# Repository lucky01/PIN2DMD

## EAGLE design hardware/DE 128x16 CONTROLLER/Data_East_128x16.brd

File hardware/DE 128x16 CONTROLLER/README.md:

# PIN2DMD - 128x16 DOT MATRIX CONTROLLER BOARD

This are the PCB files for the Dot Matrix Contoller Board like used in early Data East machines 
e.g Batman, Checkpoint, Hook, Star Trek 25th anniversary and Teenage Mutant Ninja Turtles. It is needed to connect these
machines to the PIN2DMD Nucleo shield. PCB design by Rappelbox, UncleSash and Lucky1

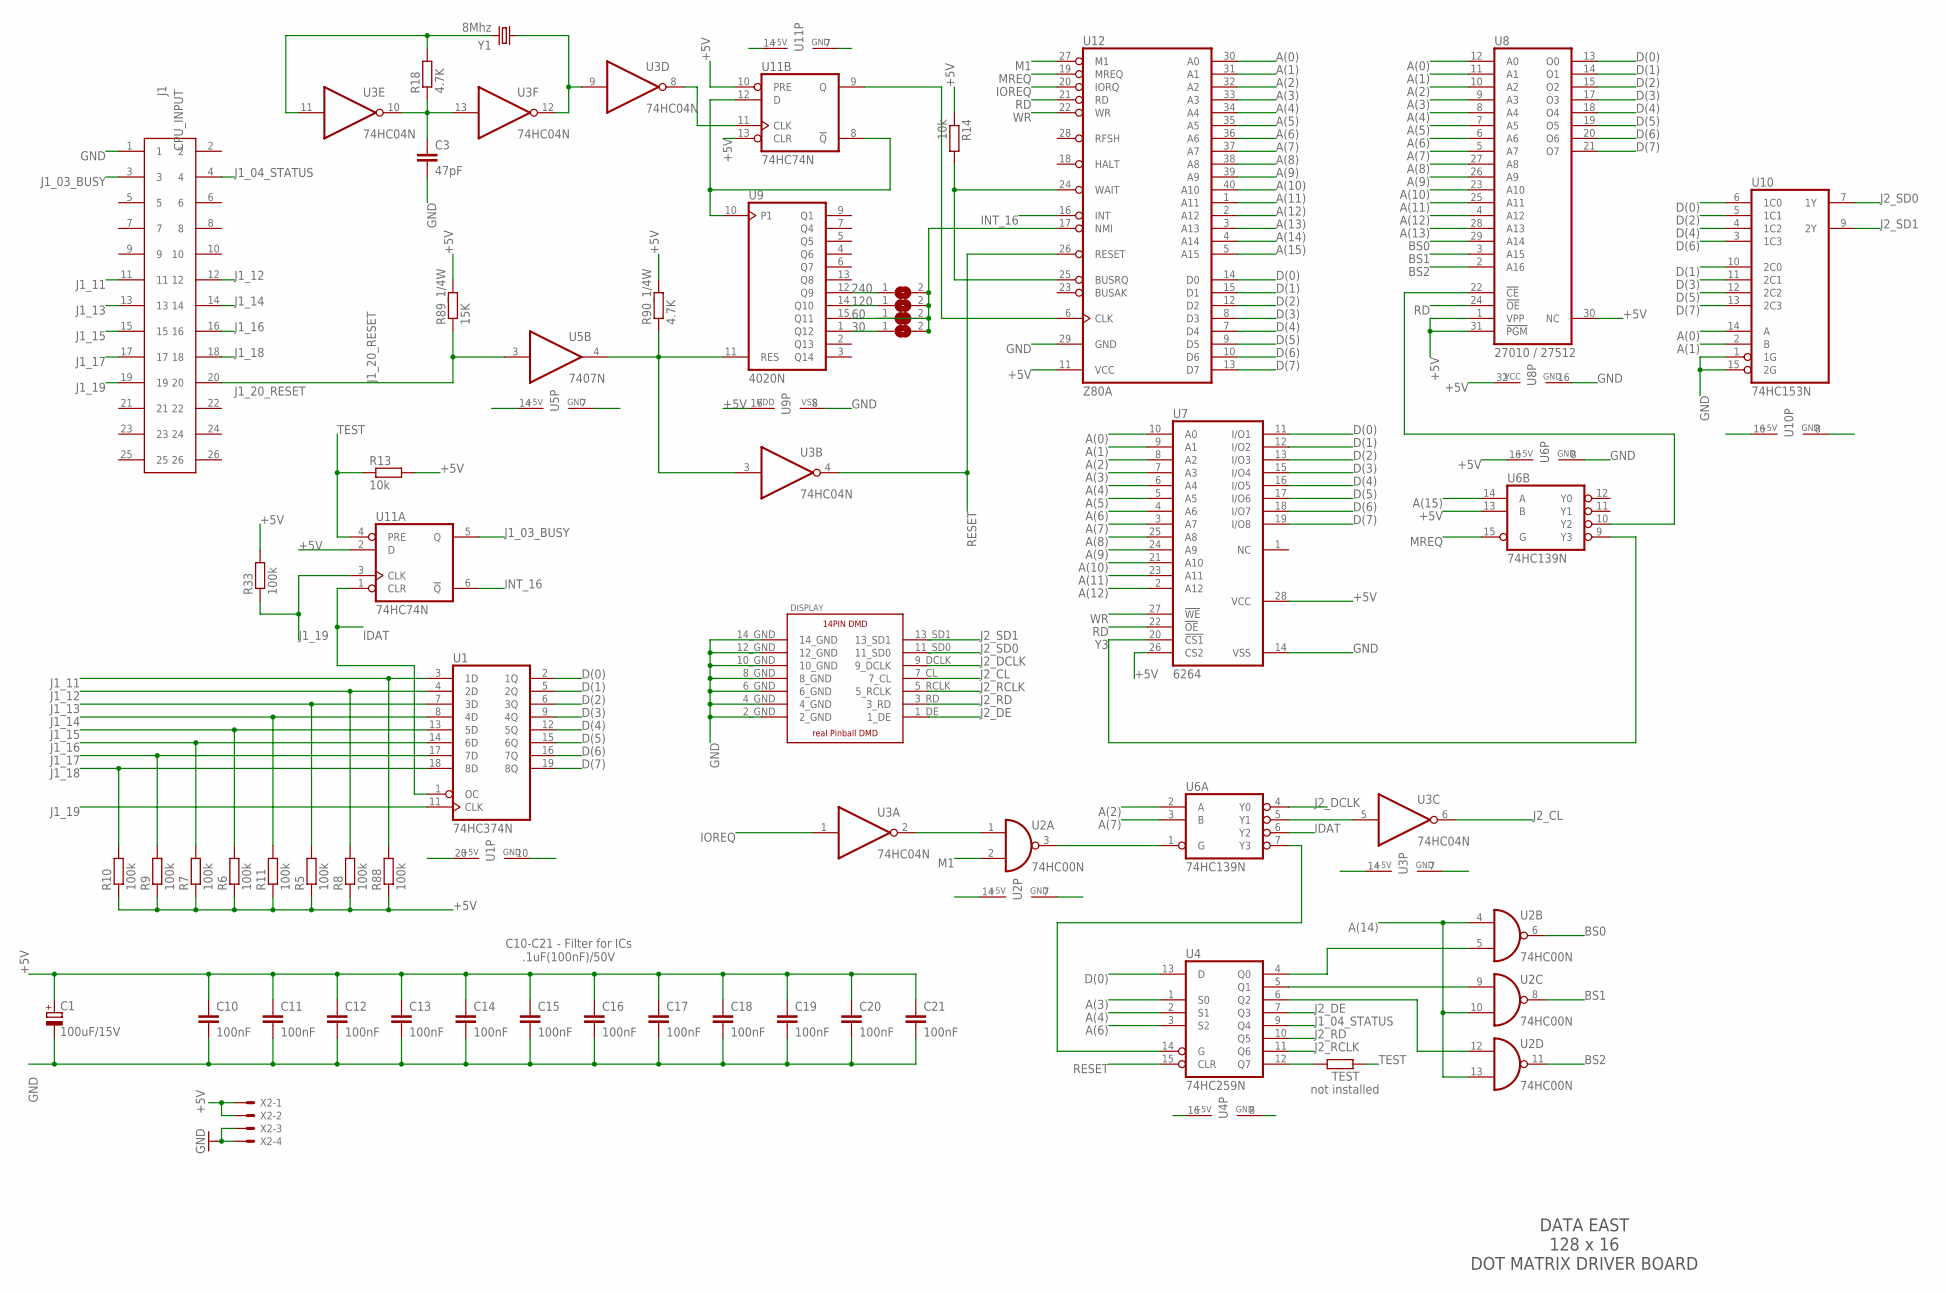
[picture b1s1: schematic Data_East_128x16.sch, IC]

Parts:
C1: 100uF/15V; E2,5-7
C3: 47pF; C050-025X075
C10, C11, C12, C13, C14, C15, C16, C17, C18, C19, C20, C21: 100nF; C050-025X075
CPU_INPUT: J1; 61202622323
DISPLAY: PINBALL_DMD_HEADER_MALE; 14_PIN_DMD_MALE
R5, R6, R7, R8, R9, R10, R11, R33, R88: 100k; 0207/7
R13, R14: 10k; 0207/7
R18, R90_1/4W: 4.7K; 0207/7
R89_1/4W: 15K; 0207/7
SJ2, SJ4, SJ5, SJ6: SJ
TEST: R-EU_0207/7; 0207/7
U1: 74HC374N; DIL20
U2: 74HC00N; DIL14
U3: 74HC04N; DIL14
U4: 74HC259N; DIL16
U5: 7407N; DIL14
U6: 74HC139N; DIL16
U7: 6264; DIL28-6
U8: 27010 / 27512; DIL32
U9: 4020N; DIL16
U10: 74HC153N; DIL16
U11: 74HC74N; DIL14
U12: Z80A; DIL40
X2: KK-156-4
Y1: 8Mhz; HC49U70

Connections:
30: SJ6.1, U9.1 (Q12)
60: SJ2.2, SJ4.2, SJ5.1, SJ5.2, SJ6.2, U9.15 (Q11), U12.17 (NMI)
120: SJ4.1, U9.14 (Q10)
240: SJ2.1, U9.12 (Q9)
+5V: C1.+, C10.1, C11.1, C12.1, C13.1, C14.1, C15.1, C16.1, C17.1, C18.1, C19.1, C20.1, C21.1, R5.1, R6.1, R7.1, R8.1, R9.1, R10.1, R11.1, R13.2, R14.1, R33.2, R88.1, R89_1/4W.2, R90_1/4W.2, U1.20 (VCC), U2.14 (VCC), U3.14 (VCC), U4.16 (VCC), U5.14 (VCC), U6.13 (B), U6.16 (VCC), U7.26 (CS2), U7.28 (VCC), U8.1 (VPP), U8.30 (NC), U8.31 (!PGM), U8.32 (VCC), U9.16 (VDD), U10.16 (VCC), U11.2 (D), U11.10 (PRE), U11.13 (CLR), U11.14 (VCC), U12.11 (VCC), X2.1, X2.2
A(0): U7.10 (A0), U8.12 (A0), U10.14 (A), U12.30 (A0)
A(1): U7.9 (A1), U8.11 (A1), U10.2 (B), U12.31 (A1)
A(2): U6.2 (A), U7.8 (A2), U8.10 (A2), U12.32 (A2)
A(3): U4.1 (S0), U7.7 (A3), U8.9 (A3), U12.33 (A3)
A(4): U4.2 (S1), U7.6 (A4), U8.8 (A4), U12.34 (A4)
A(5): U7.5 (A5), U8.7 (A5), U12.35 (A5)
A(6): U4.3 (S2), U7.4 (A6), U8.6 (A6), U12.36 (A6)
A(7): U6.3 (B), U7.3 (A7), U8.5 (A7), U12.37 (A7)
A(8): U7.25 (A8), U8.27 (A8), U12.38 (A8)
A(9): U7.24 (A9), U8.26 (A9), U12.39 (A9)
A(10): U7.21 (A10), U8.23 (A10), U12.40 (A10)
A(11): U7.23 (A11), U8.25 (A11), U12.1 (A11)
A(12): U7.2 (A12), U8.4 (A12), U12.2 (A12)
A(13): U8.28 (A13), U12.3 (A13)
A(14): U2.4 (I0), U2.10 (I1), U2.13 (I1), U12.4 (A14)
A(15): U6.14 (A), U12.5 (A15)
BS0: U2.6 (O), U8.29 (A14)
BS1: U2.8 (O), U8.3 (A15)
BS2: U2.11 (O), U8.2 (A16)
D(0): U1.2 (1Q), U4.13 (D), U7.11 (I/O1), U8.13 (O0), U10.6 (1C0), U12.14 (D0)
D(1): U1.5 (2Q), U7.12 (I/O2), U8.14 (O1), U10.10 (2C0), U12.15 (D1)
D(2): U1.6 (3Q), U7.13 (I/O3), U8.15 (O2), U10.5 (1C1), U12.12 (D2)
D(3): U1.9 (4Q), U7.15 (I/O4), U8.17 (O3), U10.11 (2C1), U12.8 (D3)
D(4): U1.12 (5Q), U7.16 (I/O5), U8.18 (O4), U10.4 (1C2), U12.7 (D4)
D(5): U1.15 (6Q), U7.17 (I/O6), U8.19 (O5), U10.12 (2C2), U12.9 (D5)
D(6): U1.16 (7Q), U7.18 (I/O7), U8.20 (O6), U10.3 (1C3), U12.10 (D6)
D(7): U1.19 (8Q), U7.19 (I/O8), U8.21 (O7), U10.13 (2C3), U12.13 (D7)
GND: C1.-, C3.2, C10.2, C11.2, C12.2, C13.2, C14.2, C15.2, C16.2, C17.2, C18.2, C19.2, C20.2, C21.2, CPU_INPUT.1, DISPLAY.2_GND, DISPLAY.4_GND, DISPLAY.6_GND, DISPLAY.8_GND, DISPLAY.10_GND, DISPLAY.12_GND, DISPLAY.14_GND, U1.10 (GND), U2.7 (GND), U3.7 (GND), U4.8 (GND), U5.7 (GND), U6.8 (GND), U7.14 (VSS), U8.16 (GND), U9.8 (VSS), U10.1 (1G), U10.8 (GND), U10.15 (2G), U11.7 (GND), U12.29 (GND), X2.3, X2.4
IDAT: U1.1 (OC), U6.6 (Y2), U11.1 (CLR)
INT_16: U11.6 (!Q), U12.16 (INT)
IOREQ: U3.1 (I), U12.20 (IORQ)
J1_03_BUSY: CPU_INPUT.3, U11.5 (Q)
J1_04_STATUS: CPU_INPUT.4, U4.9 (Q4)
J1_11: CPU_INPUT.11, R88.2, U1.3 (1D)
J1_12: CPU_INPUT.12, R8.2, U1.4 (2D)
J1_13: CPU_INPUT.13, R5.2, U1.7 (3D)
J1_14: CPU_INPUT.14, R11.2, U1.8 (4D)
J1_15: CPU_INPUT.15, R6.2, U1.13 (5D)
J1_16: CPU_INPUT.16, R7.2, U1.14 (6D)
J1_17: CPU_INPUT.17, R9.2, U1.17 (7D)
J1_18: CPU_INPUT.18, R10.2, U1.18 (8D)
J1_19: CPU_INPUT.19, R33.1, U1.11 (CLK), U11.3 (CLK)
J1_20_RESET: CPU_INPUT.20, R89_1/4W.1, U5.3 (I)
J2_CL: DISPLAY.7_CL, U3.6 (O)
J2_DCLK: DISPLAY.9_DCLK, U6.4 (Y0)
J2_DE: DISPLAY.1_DE, U4.7 (Q3)
J2_RCLK: DISPLAY.5_RCLK, U4.11 (Q6)
J2_RD: DISPLAY.3_RD, U4.10 (Q5)
J2_SD0: DISPLAY.11_SD0, U10.7 (1Y)
J2_SD1: DISPLAY.13_SD1, U10.9 (2Y)
M1: U2.2 (I1), U12.27 (M1)
MREQ: U6.15 (G), U12.19 (MREQ)
unnamed: C3.1, R18.1, U3.10 (O), U3.13 (I)
unnamed: R18.2, U3.11 (I), Y1.2
unnamed: U3.9 (I), U3.12 (O), Y1.1
unnamed: TEST.2, U4.12 (Q7)
unnamed: U3.8 (O), U11.11 (CLK)
unnamed: U9.10 (P1), U11.8 (!Q), U11.12 (D)
unnamed: R90_1/4W.1, U3.3 (I), U5.4 (O), U9.11 (RES)
unnamed: U11.9 (Q), U12.6 (CLK)
unnamed: R14.2, U12.24 (WAIT), U12.25 (BUSRQ)
unnamed: U3.5 (I), U6.5 (Y1)
unnamed: U2.5 (I1), U4.4 (Q0)
unnamed: U2.1 (I0), U3.2 (O)
unnamed: U2.3 (O), U6.1 (G)
unnamed: U2.9 (I0), U4.5 (Q1)
unnamed: U4.14 (G), U6.7 (Y3)
unnamed: U2.12 (I0), U4.6 (Q2)
unnamed: U6.10 (Y2), U8.22 (!CE)
RD: U7.22 (!OE), U8.24 (!OE), U12.21 (RD)
RESET: U3.4 (O), U4.15 (CLR), U12.26 (RESET)
TEST: R13.1, TEST.1, U11.4 (PRE)
WR: U7.27 (!WE), U12.22 (WR)
Y3: U6.9 (Y3), U7.20 (!CS1)

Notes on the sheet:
C10-C21 - Filter for ICs .1uF(100nF)/50V
DATA EAST 128 x 16 DOT MATRIX DRIVER BOARD
not installed

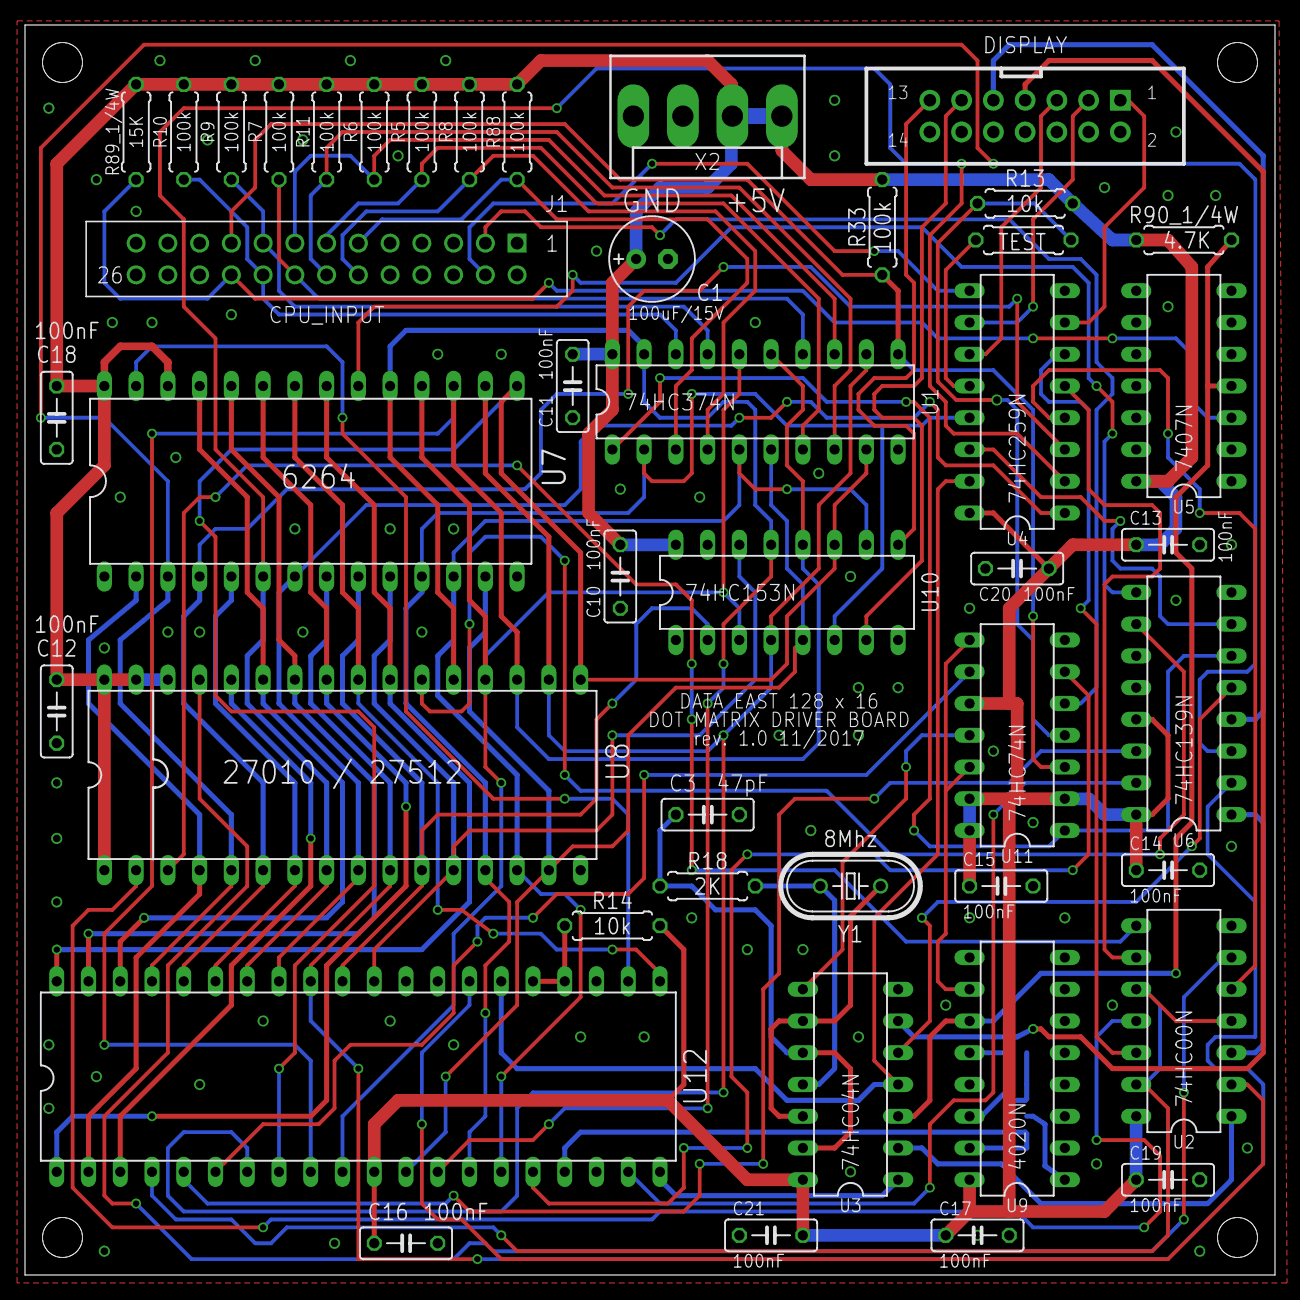
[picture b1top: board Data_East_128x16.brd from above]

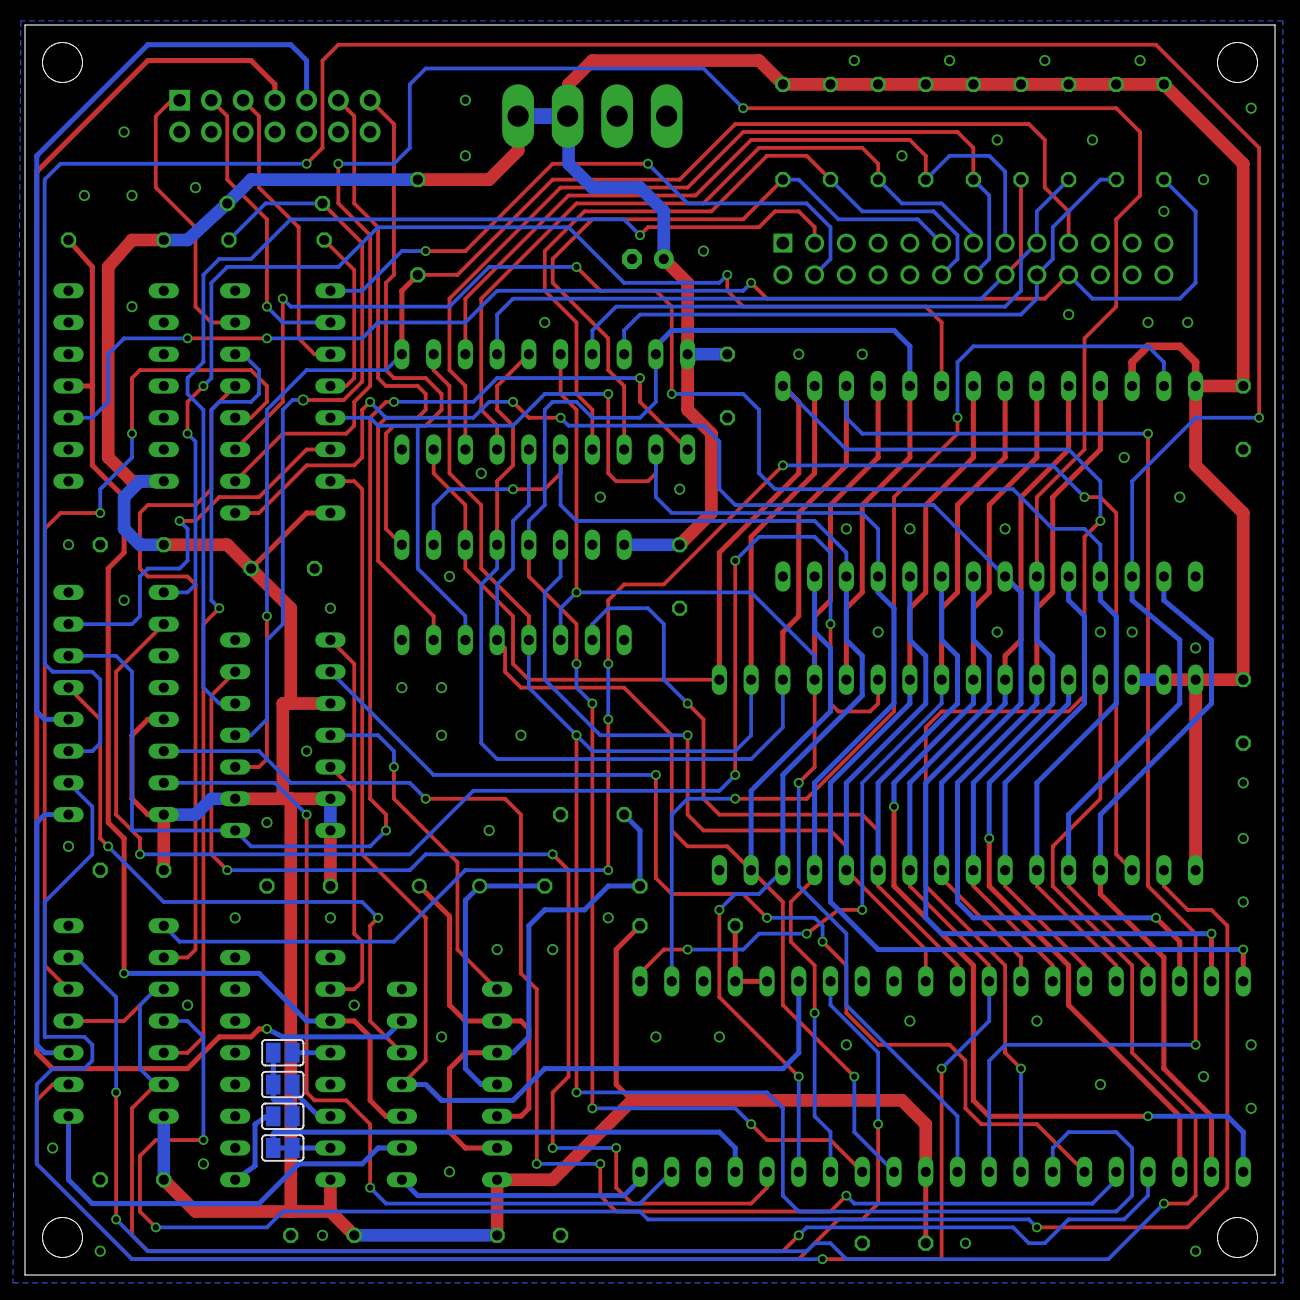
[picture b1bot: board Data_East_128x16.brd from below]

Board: 2 copper layers, 100.0 x 100.0 mm, 49 parts (4 on the bottom side), 79 nets.

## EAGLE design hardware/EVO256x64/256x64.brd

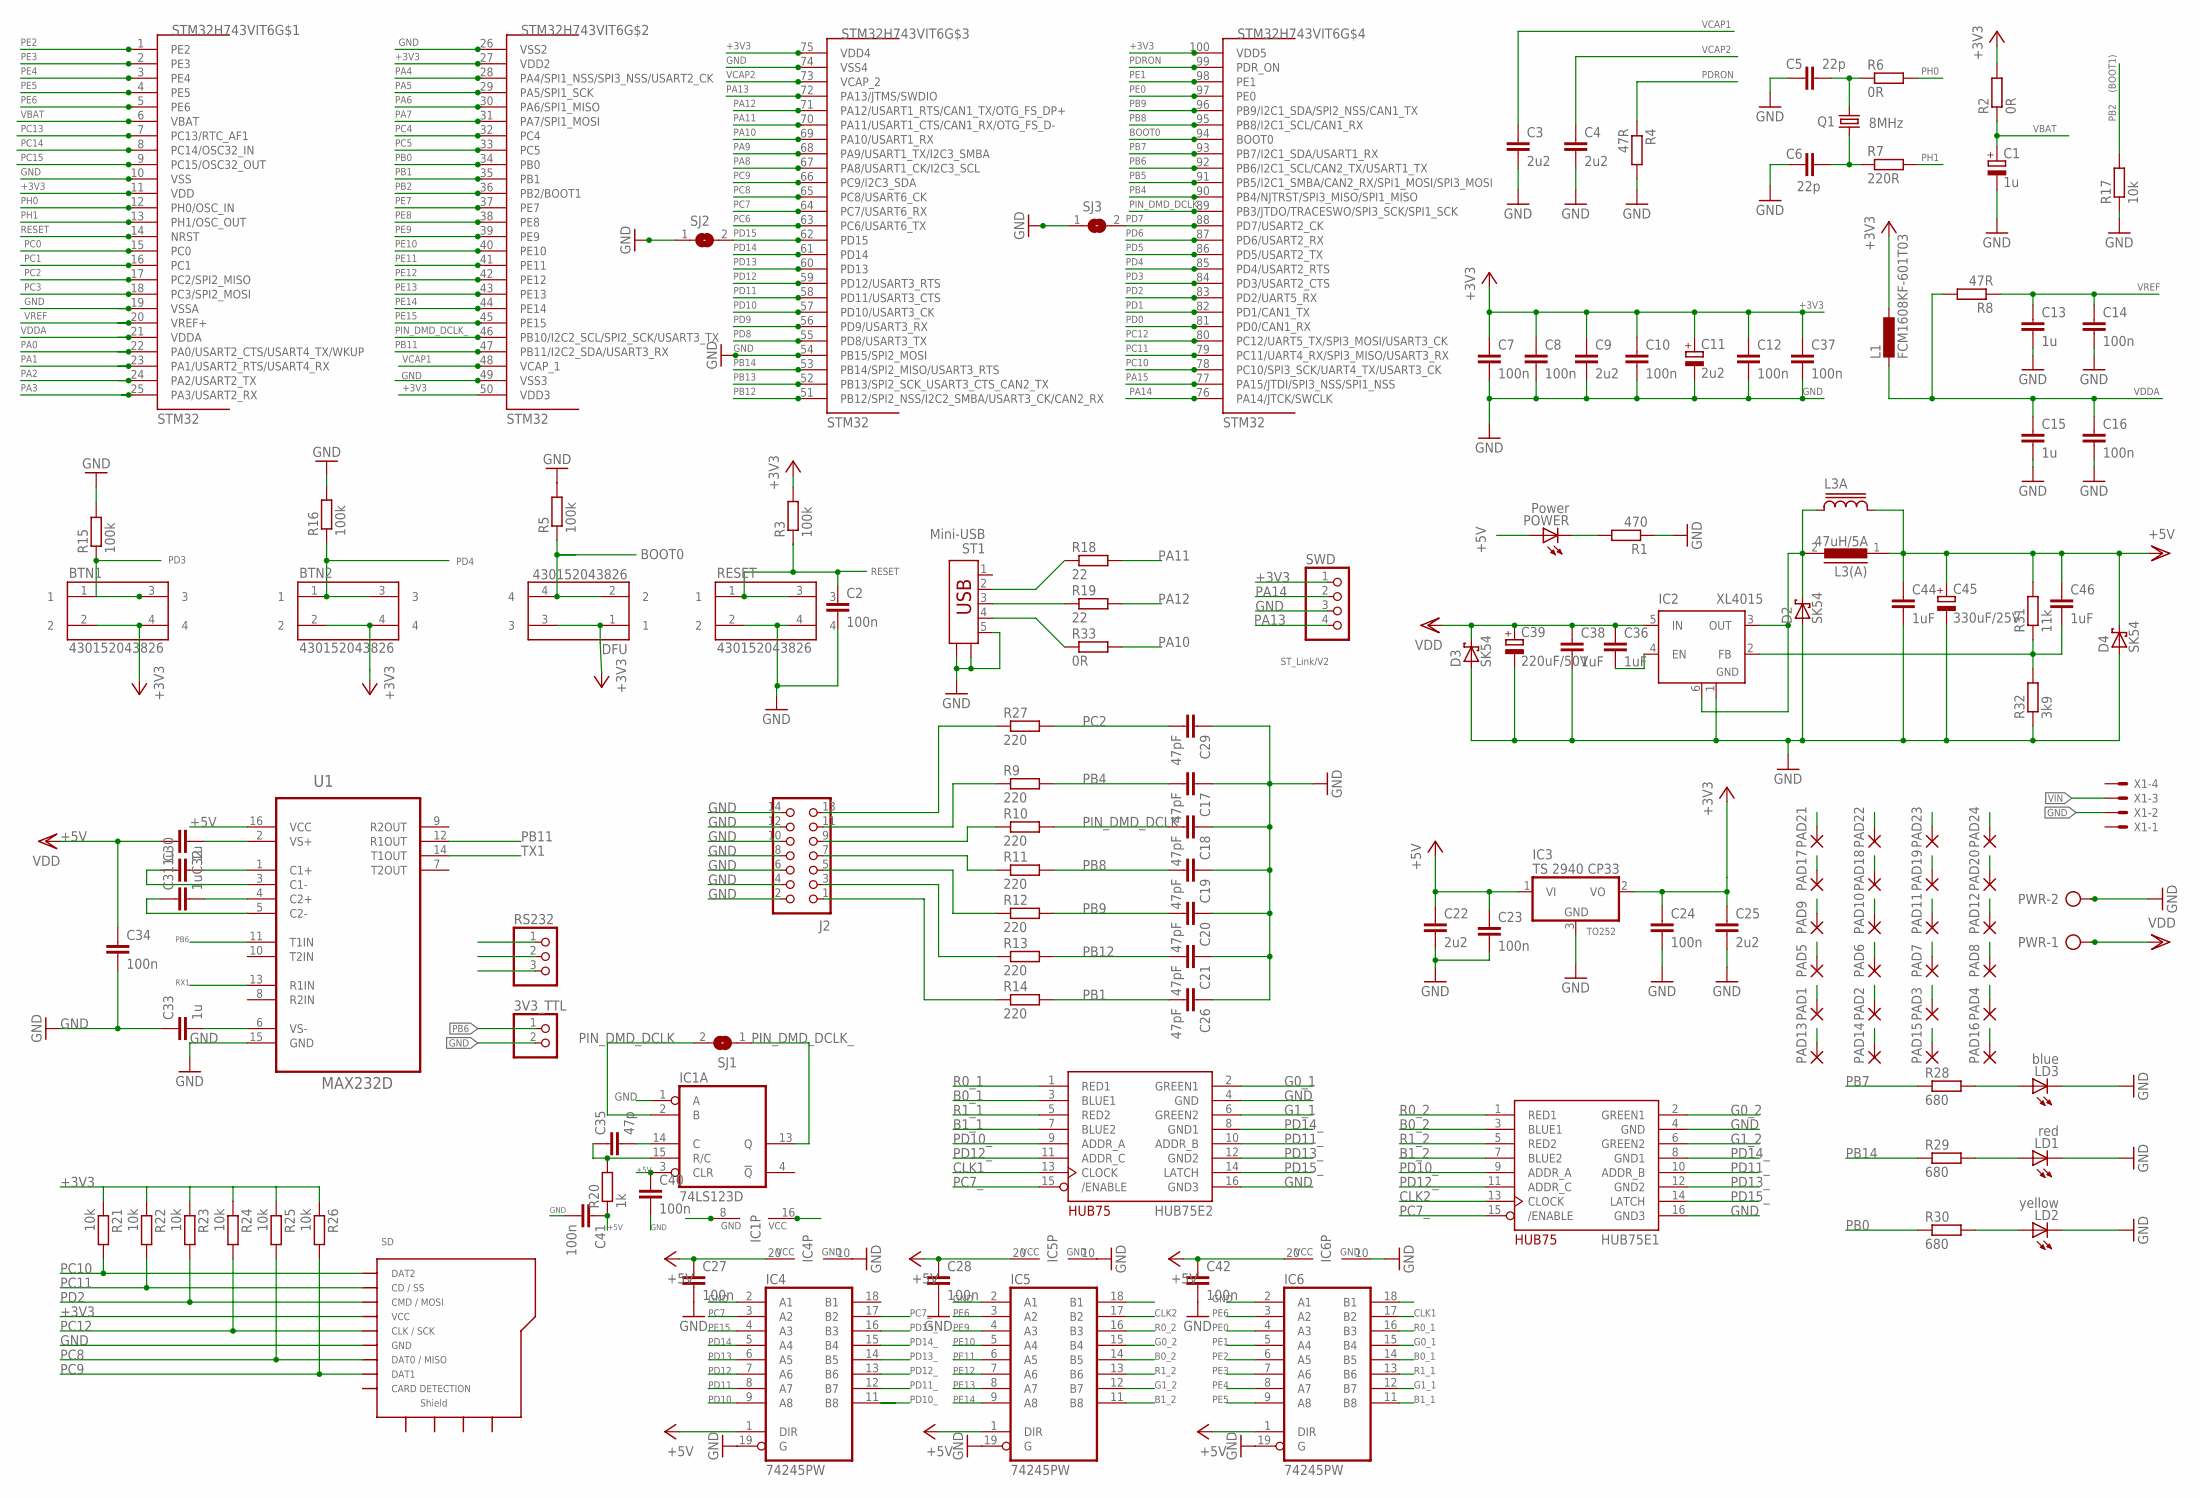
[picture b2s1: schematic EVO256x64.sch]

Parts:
3V3_TTL: PINHD-1X2; 1X02
BTN1, BTN2: 430152043826
C1: 1u; CT3528
C2, C7, C8, C10, C12, C14, C16, C23, C24, C27, C28, C34, C37, C40, C41, C42: 100n; C0805
C3, C4: 2u2; C0805
C5, C6: 22p; C0805
C9, C22, C25: 2u2; C1206
C11: 2u2; CT3528
C13, C15: 1u; C1206
C17, C18, C19, C20, C21, C26, C29: 47pF; C0805
C30, C31, C32, C33: 1u; C0805
C35: 47p; C0805
C36, C38, C44, C46: 1uF; C1206
C39: 220uF/50V; PANASONIC_G
C45: 330uF/25V; PANASONIC_G
D2, D3, D4: SK54; SMB
DFU: 430152043826
HUB75E1, HUB75E2: RGB; 2X08-IDC
IC1: 74LS123D; SO16
IC2: XL4015; TO263-5
IC3: TS 2940 CP33; TO252
IC4, IC5, IC6: 74245PW; TSSOP20
J2: CON_HEADER_2X07-PTH-SHROUDED; PINSHRD_PTH_2X07
L1: FCM1608KF-601T03; L2012C
L3(A): 47uH/5A; ED16
L3A: SRR1206
LD1: red; CHIP-LED0805
LD2: yellow; CHIP-LED0805
LD3: blue; CHIP-LED0805
PAD1, PAD2, PAD3, PAD4, PAD5, PAD6, PAD7, PAD8, PAD9, PAD10, PAD11, PAD12, PAD13, PAD14, PAD15, PAD16, PAD17, PAD18, PAD19, PAD20, PAD21, PAD22, PAD23, PAD24: SMD5; SMD2,54-5,08
POWER: Power; CHIPLED_0805
PWR: AK500/2-H
Q1: 8MHz; HC49UP
R1: 470; R0805
R2, R6, R33: 0R; R0805
R3, R5, R15, R16: 100k; R0805
R4, R8: 47R; R0805
R7: 220R; R0805
R9, R10, R11, R12, R13, R14, R27: 220; R0805
R17, R21, R22, R23, R24, R25, R26: 10k; R0805
R18, R19: 22; R0805
R20: 1k; R0805
R28, R29, R30: 680; R0805
R31: 11k; R1206
R32: 3k9; R1206
RESET: 430152043826
RS232: PINHD-1X3; 1X03
SD: MICROSD_CARD_POLLIN; MR**-AP*03**
SJ1, SJ2, SJ3: SJ
ST1: Mini-USB; USBMINI
STM32H743VIT6: STM32; LQFP100
SWD: PINHD-1X4; 1X04
U1: MAX232D; SOIC127P600X175-16N
X1: KK-156-4

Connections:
+3V3: BTN1.2, BTN1.4, BTN2.2, BTN2.4, C7.1, C8.1, C9.1, C10.1, C11.+, C12.1, C24.1, C25.1, C37.1, DFU.1, DFU.3, IC3.2 (VO), L1.1, R2.2, R3.2, R21.1, R22.1, R23.1, R24.1, R25.1, R26.1, SD.VCC, STM32H743VIT6.11 (VDD), STM32H743VIT6.27 (VDD2), STM32H743VIT6.50 (VDD3), STM32H743VIT6.75 (VDD4), STM32H743VIT6.100 (VDD5), SWD.1
+5V: C22.1, C23.1, C27.1, C28.1, C32.2, C34.1, C40.1, C41.1, C42.1, C44.1, C45.+, C46.1, D4.C, IC1.3 (CLR), IC1.16 (VCC), IC3.1 (VI), IC4.1 (DIR), IC4.20 (VCC), IC5.1 (DIR), IC5.20 (VCC), IC6.1 (DIR), IC6.20 (VCC), L3(A).1, L3A.2, PAD1.1, PAD2.1, PAD5.1, PAD6.1, PAD9.1, PAD10.1, PAD13.1, PAD14.1, PAD17.1, PAD18.1, PAD21.1, PAD22.1, POWER.A, R20.1, R31.2, U1.16 (VCC)
B0_1: HUB75E2.3 (BLUE1), IC6.14 (B5)
B0_2: HUB75E1.3 (BLUE1), IC5.14 (B5)
B1_1: HUB75E2.7 (BLUE2), IC6.11 (B8)
B1_2: HUB75E1.7 (BLUE2), IC5.11 (B8)
BOOT0: DFU.2, DFU.4, R5.1, STM32H743VIT6.94 (BOOT0)
CLK1: HUB75E2.13 (CLOCK), IC6.17 (B2)
CLK2: HUB75E1.13 (CLOCK), IC5.17 (B2)
G0_1: HUB75E2.2 (GREEN1), IC6.15 (B4)
G0_2: HUB75E1.2 (GREEN1), IC5.15 (B4)
G1_1: HUB75E2.6 (GREEN2), IC6.12 (B7)
G1_2: HUB75E1.6 (GREEN2), IC5.12 (B7)
GND: 3V3_TTL.2, C1.-, C2.2, C3.2, C4.2, C5.2, C6.2, C7.2, C8.2, C9.2, C10.2, C11.-, C12.2, C13.2, C14.2, C15.2, C16.2, C17.1, C18.1, C19.1, C20.1, C21.1, C22.2, C23.2, C24.2, C25.2, C26.1, C27.2, C28.2, C29.1, C33.1, C34.2, C37.2, C38.2, C39.-, C40.2, C41.2, C42.2, C44.2, C45.-, D2.A, D3.A, D4.A, HUB75E1.4 (GND), HUB75E1.16 (GND3), HUB75E2.4 (GND), HUB75E2.16 (GND3), IC1.1 (A), IC1.8 (GND), IC2.1 (GND), IC3.3 (GND), IC4.2 (A1), IC4.10 (GND), IC4.19 (G), IC5.2 (A1), IC5.10 (GND), IC5.19 (G), IC6.2 (A1), IC6.10 (GND), IC6.19 (G), J2.2, J2.4, J2.6, J2.8, J2.10, J2.12, J2.14, LD1.C, LD2.C, LD3.C, PAD3.1, PAD4.1, PAD7.1, PAD8.1, PAD11.1, PAD12.1, PAD15.1, PAD16.1, PAD19.1, PAD20.1, PAD23.1, PAD24.1, PWR.2, R1.1, R4.2, R5.2, R15.2, R16.2, R17.1, R32.1, RESET.2, RESET.4, RS232.2, SD.GND, SJ2.1, SJ3.1, ST1.5, ST1.N1, ST1.N2, STM32H743VIT6.10 (VSS), STM32H743VIT6.19 (VSSA), STM32H743VIT6.26 (VSS2), STM32H743VIT6.49 (VSS3), STM32H743VIT6.54 (PB15/SPI2_MOSI), STM32H743VIT6.74 (VSS4), SWD.3, U1.15 (GND), X1.2
unnamed: C5.1, Q1.2, R6.1
unnamed: C6.1, Q1.1, R7.1
unnamed: POWER.C, R1.2
unnamed: J2.13, R27.1
unnamed: J2.11, R9.1
unnamed: J2.9, R10.1
unnamed: J2.7, R11.1
unnamed: J2.5, R12.1
unnamed: J2.3, R13.1
unnamed: C35.1, IC1.15 (R/C), R20.2
unnamed: J2.1, R14.1
unnamed: C30.2, U1.1 (C1+)
unnamed: C30.1, U1.3 (C1-)
unnamed: C31.2, U1.4 (C2+)
unnamed: C31.1, U1.5 (C2-)
unnamed: C33.2, U1.6 (VS-)
unnamed: C32.1, U1.2 (VS+)
unnamed: LD1.A, R29.2
unnamed: D2.C, IC2.3 (OUT), IC2.6 (TAB), L3(A).2, L3A.1
unnamed: C46.2, IC2.2 (FB), R31.1, R32.2
unnamed: C35.2, IC1.14 (C)
unnamed: LD3.A, R28.2
unnamed: C36.2, IC2.4 (EN)
unnamed: R33.1, ST1.4
unnamed: LD2.A, R30.2
unnamed: R19.1, ST1.3
unnamed: R18.1, ST1.2
PA0: STM32H743VIT6.22 (PA0/USART2_CTS/USART4_TX/WKUP)
PA1: STM32H743VIT6.23 (PA1/USART2_RTS/USART4_RX)
PA2: STM32H743VIT6.24 (PA2/USART2_TX)
PA3: STM32H743VIT6.25 (PA3/USART2_RX)
PA4: STM32H743VIT6.28 (PA4/SPI1_NSS/SPI3_NSS/USART2_CK)
PA5: STM32H743VIT6.29 (PA5/SPI1_SCK)
PA6: STM32H743VIT6.30 (PA6/SPI1_MISO)
PA7: STM32H743VIT6.31 (PA7/SPI1_MOSI)
PA8: STM32H743VIT6.67 (PA8/USART1_CK/I2C3_SCL)
PA9: STM32H743VIT6.68 (PA9/USART1_TX/I2C3_SMBA)
PA10: R33.2, STM32H743VIT6.69 (PA10/USART1_RX)
PA11: R18.2, STM32H743VIT6.70 (PA11/USART1_CTS/CAN1_RX/OTG_FS_D-)
PA12: R19.2, STM32H743VIT6.71 (PA12/USART1_RTS/CAN1_TX/OTG_FS_DP+)
PA13: STM32H743VIT6.72 (PA13/JTMS/SWDIO), SWD.4
PA14: STM32H743VIT6.76 (PA14/JTCK/SWCLK), SWD.2
PA15: STM32H743VIT6.77 (PA15/JTDI/SPI3_NSS/SPI1_NSS)
PB0: R30.1, STM32H743VIT6.34 (PB0)
PB1: C26.2, R14.2, STM32H743VIT6.35 (PB1)
PB2: R17.2, STM32H743VIT6.36 (PB2/BOOT1)
PB4: C17.2, R9.2, STM32H743VIT6.90 (PB4/NJTRST/SPI3_MISO/SPI1_MISO)
PB5: STM32H743VIT6.91 (PB5/I2C1_SMBA/CAN2_RX/SPI1_MOSI/SPI3_MO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)
PB6: 3V3_TTL.1, STM32H743VIT6.92 (PB6/I2C1_SCL/CAN2_TX/USART1_TX), U1.11 (T1IN)
PB7: R28.1, STM32H743VIT6.93 (PB7/I2C1_SDA/USART1_RX)
PB8: C19.2, R11.2, STM32H743VIT6.95 (PB8/I2C1_SCL/CAN1_RX)
PB9: C20.2, R12.2, STM32H743VIT6.96 (PB9/I2C1_SDA/SPI2_NSS/CAN1_TX)
PB11: STM32H743VIT6.47 (PB11/I2C2_SDA/USART3_RX), U1.12 (R1OUT)
PB12: C21.2, R13.2, STM32H743VIT6.51 (PB12/SPI2_NSS/I2C2_SMBA/USART3_CK/CAN2_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)
PB13: STM32H743VIT6.52 (PB13/SPI2_SCK_USART3_CTS_CAN2_TX)
PB14: R29.1, STM32H743VIT6.53 (PB14/SPI2_MISO/USART3_RTS)
PC0: STM32H743VIT6.15 (PC0)
PC1: STM32H743VIT6.16 (PC1)
PC2: C29.2, R27.2, STM32H743VIT6.17 (PC2/SPI2_MISO)
PC3: STM32H743VIT6.18 (PC3/SPI2_MOSI)
PC4: STM32H743VIT6.32 (PC4)
PC5: STM32H743VIT6.33 (PC5)
PC6: STM32H743VIT6.63 (PC6/USART6_TX)
PC7: IC4.3 (A2), STM32H743VIT6.64 (PC7/USART6_RX)
PC7_: HUB75E1.15 (/ENABLE), HUB75E2.15 (/ENABLE), IC4.17 (B2)
PC8: R25.2, SD.DAT0 (DAT0/MISO), STM32H743VIT6.65 (PC8/USART6_CK)
PC9: R26.2, SD.DAT1, STM32H743VIT6.66 (PC9/I2C3_SDA)
PC10: R21.2, SD.DAT2, STM32H743VIT6.78 (PC10/SPI3_SCK/UART4_TX/USART3_CK)
PC11: R22.2, SD.DAT3/CS (CD/SS), STM32H743VIT6.79 (PC11/UART4_RX/SPI3_MISO/USART3_RX)
PC12: R24.2, SD.CLK (CLK/SCK), STM32H743VIT6.80 (PC12/UART5_TX/SPI3_MOSI/USART3_CK)
PC13: STM32H743VIT6.7 (PC13/RTC_AF1)
PC14: STM32H743VIT6.8 (PC14/OSC32_IN)
PC15: STM32H743VIT6.9 (PC15/OSC32_OUT)
PD0: STM32H743VIT6.81 (PD0/CAN1_RX)
PD1: STM32H743VIT6.82 (PD1/CAN1_TX)
PD2: R23.2, SD.CMD (CMD/MOSI), STM32H743VIT6.83 (PD2/UART5_RX)
PD3: BTN1.1, BTN1.3, R15.1, STM32H743VIT6.84 (PD3/USART2_CTS)
PD4: BTN2.1, BTN2.3, R16.1, STM32H743VIT6.85 (PD4/USART2_RTS)
PD5: STM32H743VIT6.86 (PD5/USART2_TX)
PD6: STM32H743VIT6.87 (PD6/USART2_RX)
PD7: SJ3.2, STM32H743VIT6.88 (PD7/USART2_CK)
PD8: STM32H743VIT6.55 (PD8/USART3_TX)
PD9: STM32H743VIT6.56 (PD9/USART3_RX)
PD10: IC4.9 (A8), STM32H743VIT6.57 (PD10/USART3_CK)
PD10_: HUB75E1.9 (ADDR_A), HUB75E2.9 (ADDR_A), IC4.11 (B8)
PD11: IC4.8 (A7), STM32H743VIT6.58 (PD11/USART3_CTS)
PD11_: HUB75E1.10 (ADDR_B), HUB75E2.10 (ADDR_B), IC4.12 (B7)
PD12: IC4.7 (A6), STM32H743VIT6.59 (PD12/USART3_RTS)
PD12_: HUB75E1.11 (ADDR_C), HUB75E2.11 (ADDR_C), IC4.13 (B6)
PD13: IC4.6 (A5), STM32H743VIT6.60 (PD13)
PD13_: HUB75E1.12 (GND2), HUB75E2.12 (GND2), IC4.14 (B5)
PD14: IC4.5 (A4), STM32H743VIT6.61 (PD14)
PD14_: HUB75E1.8 (GND1), HUB75E2.8 (GND1), IC4.15 (B4)
PD15: SJ2.2, STM32H743VIT6.62 (PD15)
PD15_: HUB75E1.14 (LATCH), HUB75E2.14 (LATCH), IC4.16 (B3)
PDRON: R4.1, STM32H743VIT6.99 (PDR_ON)
PE0: IC6.4 (A3), STM32H743VIT6.97 (PE0)
PE1: IC6.5 (A4), STM32H743VIT6.98 (PE1)
PE2: IC6.6 (A5), STM32H743VIT6.1 (PE2)
PE3: IC6.7 (A6), STM32H743VIT6.2 (PE3)
PE4: IC6.8 (A7), STM32H743VIT6.3 (PE4)
PE5: IC6.9 (A8), STM32H743VIT6.4 (PE5)
PE6: IC5.3 (A2), IC6.3 (A2), STM32H743VIT6.5 (PE6)
PE7: STM32H743VIT6.37 (PE7)
PE8: STM32H743VIT6.38 (PE8)
PE9: IC5.4 (A3), STM32H743VIT6.39 (PE9)
PE10: IC5.5 (A4), STM32H743VIT6.40 (PE10)
PE11: IC5.6 (A5), STM32H743VIT6.41 (PE11)
PE12: IC5.7 (A6), STM32H743VIT6.42 (PE12)
PE13: IC5.8 (A7), STM32H743VIT6.43 (PE13)
PE14: IC5.9 (A8), STM32H743VIT6.44 (PE14)
PE15: IC4.4 (A3), STM32H743VIT6.45 (PE15)
PH0: R6.2, STM32H743VIT6.12 (PH0/OSC_IN)
PH1: R7.2, STM32H743VIT6.13 (PH1/OSC_OUT)
PIN_DMD_DCLK: C18.2, IC1.2 (B), R10.2, SJ1.2
PIN_DMD_DCLK_: IC1.13 (Q), SJ1.1, STM32H743VIT6.46 (PB10/I2C2_SCL/SPI2_SCK/USART3_TX), STM32H743VIT6.89 (PB3/JTDO/TRACESWO/SPI3_SCK/SPI1_SCK)
R0_1: HUB75E2.1 (RED1), IC6.16 (B3)
R0_2: HUB75E1.1 (RED1), IC5.16 (B3)
R1_1: HUB75E2.5 (RED2), IC6.13 (B6)
R1_2: HUB75E1.5 (RED2), IC5.13 (B6)
RESET: C2.1, R3.1, RESET.1, RESET.3, STM32H743VIT6.14 (NRST)
RX1: RS232.3, U1.13 (R1IN)
TX1: RS232.1, U1.14 (T1OUT)
VBAT: C1.+, R2.1, STM32H743VIT6.6 (VBAT)
VCAP1: C3.1, STM32H743VIT6.48 (VCAP_1)
VCAP2: C4.1, STM32H743VIT6.73 (VCAP_2)
VDDA: C15.1, C16.1, L1.2, R8.2, STM32H743VIT6.21 (VDDA)
VIN: C36.1, C38.1, C39.+, D3.C, IC2.5 (IN), PWR.1, X1.3
VREF: C13.1, C14.1, R8.1, STM32H743VIT6.20 (VREF+)

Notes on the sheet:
TO252
(BOOT1)
ST_Link/V2

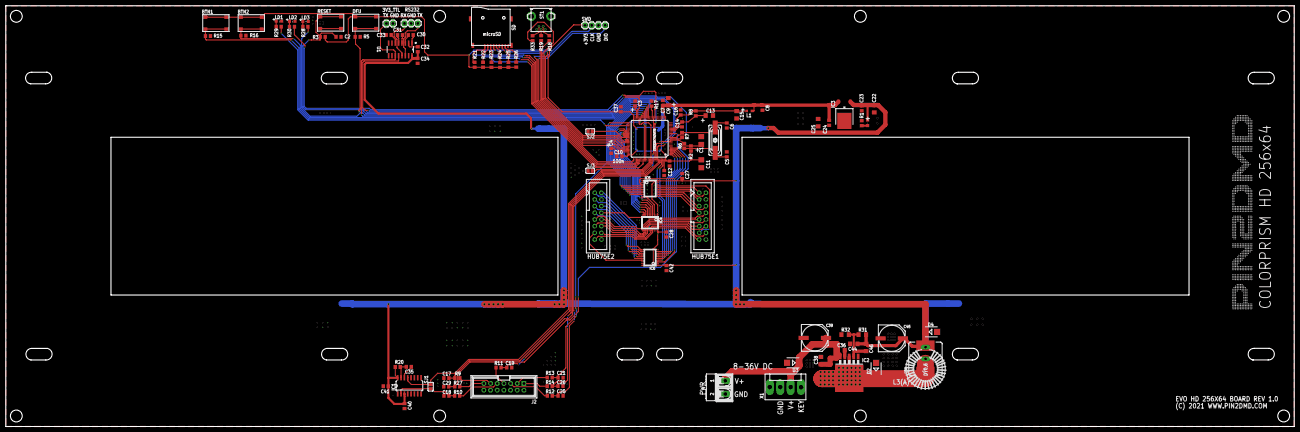
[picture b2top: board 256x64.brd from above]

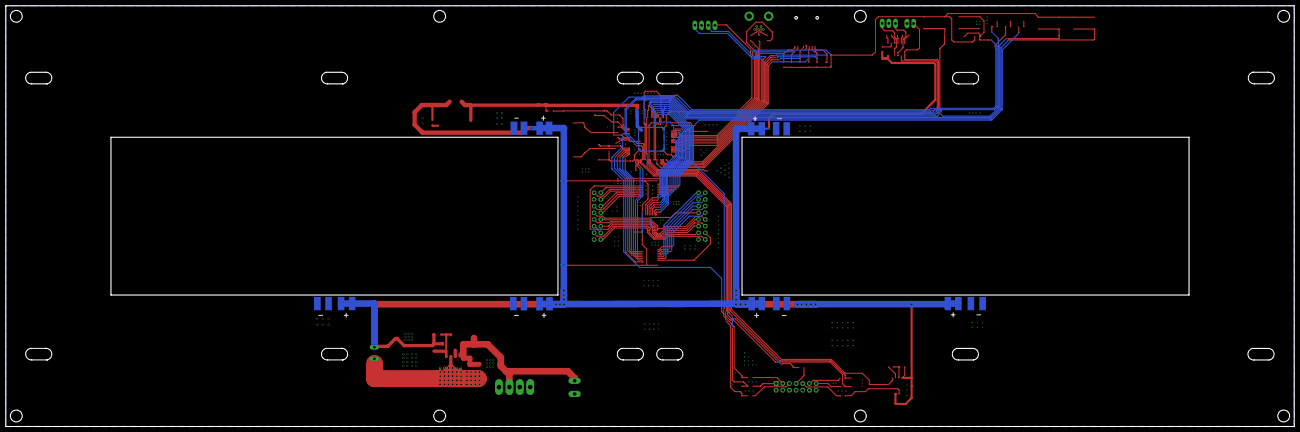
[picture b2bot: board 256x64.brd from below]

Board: 2 copper layers, 490.0 x 160.0 mm, 138 parts (24 on the bottom side), 113 nets.

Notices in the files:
hardware/EVO256x64/256x64.brd:
(C) 2021 WWW.PIN2DMD.COM
hardware/V4 NUCLEO-144/WaveShare SD reader/PIN2DMD_Nucleo144.brd:
(c) 2017 www.pin2dmd.com
parts and their libraries:
Wuerth_Elektronik_eiCan_05_Box_Header_ID: Copyright: Würth Elektronik
inductor-bourns: Copyright (C) 2008, Bob Starr
STM32F407Vx_LQFP100: Copyright 2012 by Ersan Günes, Quantitec, info@quantitec.de
